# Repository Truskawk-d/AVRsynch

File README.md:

Gra: Sekwencja Przyciskiem

Gra logiczna pozwalająca użytkownikowi na odtworzenie zaprogramowanej sekwencji przycisków. Jeśli gracz wprowadzi poprawną sekwencję w określonym czasie, gra sygnalizuje sukces. W przypadku błędu lub upływu czasu pojawia się sygnał niepowodzenia.

Funkcjonalności
	•	Tryb gry:
	•	Gracz ma za zadanie odtworzyć wcześniej ustaloną sekwencję przycisków.
	•	Limit czasu na odtworzenie całej sekwencji wynosi 10 sekund.
	•	Sukces sygnalizowany jest zapaleniem diody LED Sukces.
	•	Niepowodzenie sygnalizowane jest zapaleniem diody LED Fail.
	•	Tryb konfiguracji sekwencji:
	•	Użytkownik może ustawić własną sekwencję przycisków (4 kroki) za pomocą przycisku konfiguracji.
	•	Nowa sekwencja jest zapamiętywana do następnej konfiguracji.

Wymagania sprzętowe
	•	Mikrokontroler (np. Arduino lub zgodny z AVR)
	•	Przyciski podłączone do portów PD0–PD5
	•	Dwie diody LED (sukces i niepowodzenie) podłączone do PB1 i PB2

Sposób działania
	1.	Start gry:
	•	Naciśnij przycisk start (PD0), aby rozpocząć grę.
	•	Odtwórz zaprogramowaną sekwencję przycisków w odpowiedniej kolejności.
	•	Na poprawną sekwencję masz 10 sekund.
	2.	Konfiguracja sekwencji:
	•	Naciśnij przycisk konfiguracji (PD5), aby przejść do trybu ustawień.
	•	Ustaw nową sekwencję wciskając kolejno cztery przyciski (PD1–PD4).
	•	Po zakończeniu konfiguracji dioda LED Sukces miga dwukrotnie.

Ustawienia
	•	Domyślna sekwencja:
	•	PD1 → PD2 → PD3 → PD4
	•	Czas na wykonanie sekwencji: 10 sekund

Instalacja
	1.	Skopiuj kod do środowiska Arduino IDE lub innego kompatybilnego środowiska.
	2.	Podłącz mikrokontroler według opisanych w kodzie połączeń.
	3.	Wgraj kod na mikrokontroler.

Schemat podłączenia
	•	Przyciski:
	•	PD0: Start gry
	•	PD1–PD4: Kolejne kroki sekwencji
	•	PD5: Tryb konfiguracji
	•	Diody LED:
	•	PB1: Sukces
	•	PB2: Niepowodzenie

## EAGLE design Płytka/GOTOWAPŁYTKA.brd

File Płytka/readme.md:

# Opis płytki PCB

Płytka zaprojektowana do gry z sekwencją przycisków wykorzystuje mikrokontroler AVR (np. ATmega8) i zestaw elementów wspomagających. Oto szczegóły konstrukcji:

## 1. Mikrokontroler
- Centralnym elementem płytki jest mikrokontroler (ATmega8 lub kompatybilny) umieszczony w podstawce DIP28.
- Mikrokontroler jest podłączony do:
  - **Pinów wejściowych**: przyciski podłączone do portu **PD**.
  - **Pinów wyjściowych**: diody LED podłączone do portu **PB**.
  - Kwarcu oscylacyjnego i kondensatorów do generowania zegara.

## 2. Zasilanie
- Płytka jest zasilana poprzez stabilizator napięcia 7805, który zapewnia stabilne 5V dla mikrokontrolera i reszty układu.
- Elementy w układzie zasilania:
  - Kondensatory filtrujące (elektrolityczne i ceramiczne).
  - Diody prostownicze zabezpieczające przed odwrotną polaryzacją.
  - Dławik, który dodatkowo wygładza napięcie zasilania.

## 3. Przyciski
- Na płytce znajduje się 6 przycisków:
  - Jeden do rozpoczęcia gry (PD0).
  - Cztery do odtwarzania sekwencji (PD1–PD4).
  - Jeden do konfiguracji sekwencji (PD5).
- Przyciski są podłączone do portu D mikrokontrolera, a ich stany są odczytywane w kodzie.

## 4. Diody LED
- Na płytce znajdują się dwie diody LED:
  - **LED Sukces**: Podłączona do PB1. Sygnalizuje poprawne odtworzenie sekwencji.
  - **LED Fail**: Podłączona do PB2. Sygnalizuje błędne odtworzenie sekwencji lub upływ czasu.
- Każda dioda ma rezystor ograniczający prąd.

## 5. Oscylator kwarcowy
- Mikrokontroler korzysta z zewnętrznego oscylatora kwarcowego (16 MHz) oraz dwóch kondensatorów ceramicznych (22 pF) do stabilizacji sygnału zegarowego.

## 6. Złącza
- Płytka zawiera następujące złącza:
  - Złącze ISP (In-System Programming) do programowania mikrokontrolera.
  - Złącza zasilania (VCC i GND) dla stabilizatora.
  - Złącza pinów mikrokontrolera wyprowadzone na zewnątrz w celach testowych lub dalszej rozbudowy.

## 7. Elementy zabezpieczające
- Diody i kondensatory filtrujące w układzie zasilania zapewniają ochronę przed zakłóceniami i odwrotnym podłączeniem zasilania.

## 8. Rozmieszczenie na PCB
- Wszystkie elementy zostały rozmieszczone kompaktowo, z minimalizacją długości ścieżek krytycznych (np. dla zasilania).
- Mikrokontroler znajduje się w centralnej części płytki, otoczony przez złącza ISP i elementy wspomagające.
- Przyciski i diody LED są umieszczone w logicznych sekcjach dla łatwego dostępu.

## 9. Sposób montażu
- Wszystkie elementy zostały zaprojektowane jako przewlekane (THT), co ułatwia lutowanie.
- Płytka zawiera opisy elementów (silkscreen), co znacznie ułatwia montaż i identyfikację komponentów.

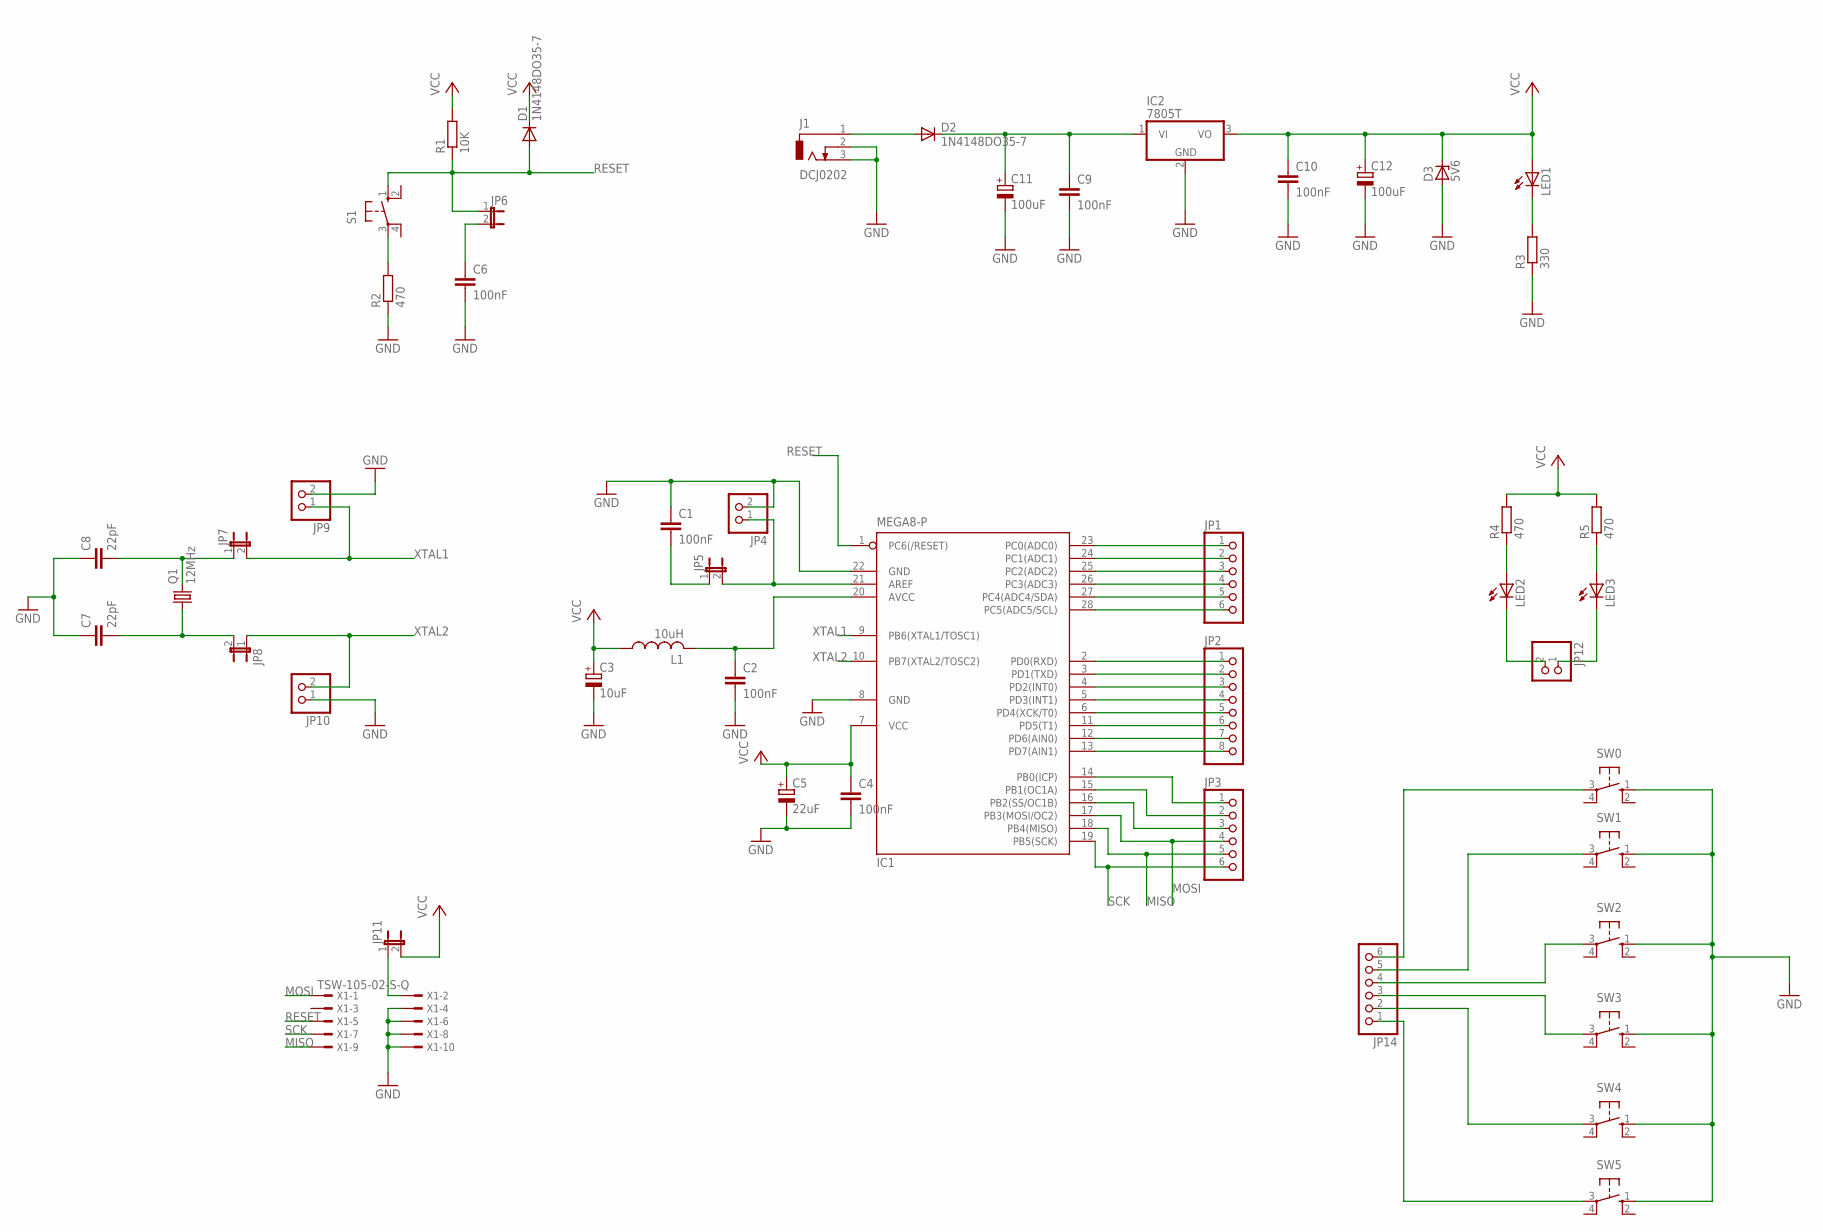
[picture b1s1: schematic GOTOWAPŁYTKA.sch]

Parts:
C1, C2, C4, C6, C9, C10: 100nF; C025-025X050
C3: 10uF; B45181B
C5: 22uF; B45181B
C7, C8: 22pF; C025-025X050
C11, C12: 100uF; B45181B
D1, D2: 1N4148DO35-7; DO35-7
D3: 5V6; C1702-15
IC1: MEGA8-P; DIL28-3
IC2: 7805T; TO220H
J1: DCJ0202
JP1, JP3, JP14: PINHD-1X6; 1X06
JP2: PINHD-1X8; 1X08
JP4, JP9, JP10, JP12: PINHD-1X2; 1X02
JP5, JP6, JP7, JP8, JP11: JP1E; JP1
L1: 10uH; 0204/7
LED1, LED2, LED3: LED5MM
Q1: 12MHz; HC49U-V
R1: 10K; 0204/7
R2, R4, R5: 470; 0204/7
R3: 330; 0204/7
S1: 10-XX; B3F-10XX
SW0, SW1, SW2, SW3, SW4, SW5: 10-XX; B3F-10XX
X1: TSW-105-02-S-Q

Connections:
GND: C1.1, C2.2, C3.-, C4.2, C5.-, C6.2, C7.1, C8.1, C9.2, C10.2, C11.-, C12.-, D3.A, IC1.8 (GND), IC1.22 (GND), IC2.2 (GND), J1.2, J1.3, JP4.2, JP9.2, JP10.1, R2.1, R3.1, SW0.1 (S), SW1.1 (S), SW2.1 (S), SW3.1 (S), SW4.1 (S), SW5.1 (S), X1.4, X1.6, X1.8, X1.10
MISO: IC1.18 (PB4(MISO)), JP3.5, X1.9
MOSI: IC1.17 (PB3(MOSI/OC2)), JP3.4, X1.1
unnamed: C2.1, IC1.20 (AVCC), L1.2
unnamed: C8.2, JP7.1, Q1.2
unnamed: C7.2, JP8.2, Q1.1
unnamed: JP11.1, X1.2
unnamed: IC1.21 (AREF), JP4.1, JP5.2
unnamed: C1.2, JP5.1
unnamed: LED1.K (C), R3.2
unnamed: D2.A, J1.1
unnamed: IC1.23 (PC0(ADC0)), JP1.1
unnamed: IC1.24 (PC1(ADC1)), JP1.2
unnamed: IC1.25 (PC2(ADC2)), JP1.3
unnamed: IC1.26 (PC3(ADC3)), JP1.4
unnamed: IC1.27 (PC4(ADC4/SDA)), JP1.5
unnamed: IC1.28 (PC5(ADC5/SCL)), JP1.6
unnamed: IC1.2 (PD0(RXD)), JP2.1
unnamed: IC1.3 (PD1(TXD)), JP2.2
unnamed: IC1.4 (PD2(INT0)), JP2.3
unnamed: IC1.5 (PD3(INT1)), JP2.4
unnamed: IC1.6 (PD4(XCK/T0)), JP2.5
unnamed: IC1.11 (PD5(T1)), JP2.6
unnamed: IC1.12 (PD6(AIN0)), JP2.7
unnamed: IC1.13 (PD7(AIN1)), JP2.8
unnamed: IC1.14 (PB0(ICP)), JP3.1
unnamed: IC1.15 (PB1(OC1A)), JP3.2
unnamed: IC1.16 (PB2(SS/OC1B)), JP3.3
unnamed: C9.1, C11.+, D2.C, IC2.1 (VI)
unnamed: JP12.1, LED3.K (C)
unnamed: LED3.A, R5.1
unnamed: R2.2, S1.3
unnamed: C6.1, JP6.2
unnamed: JP12.2, LED2.K (C)
unnamed: LED2.A, R4.1
unnamed: JP14.5, SW1.3
unnamed: JP14.4, SW2.3
unnamed: JP14.3, SW3.3
unnamed: JP14.2, SW4.3
unnamed: JP14.6, SW0.3
unnamed: JP14.1, SW5.3
RESET: D1.A, IC1.1 (PC6(/RESET)), JP6.1, R1.1, S1.1 (S), X1.5
SCK: IC1.19 (PB5(SCK)), JP3.6, X1.7
VCC: C3.+, C4.1, C5.+, C10.1, C12.+, D1.C, D3.C, IC1.7 (VCC), IC2.3 (VO), JP11.2, L1.1, LED1.A, R1.2, R4.2, R5.2
XTAL1: IC1.9 (PB6(XTAL1/TOSC1)), JP7.2, JP9.1
XTAL2: IC1.10 (PB7(XTAL2/TOSC2)), JP8.1, JP10.2

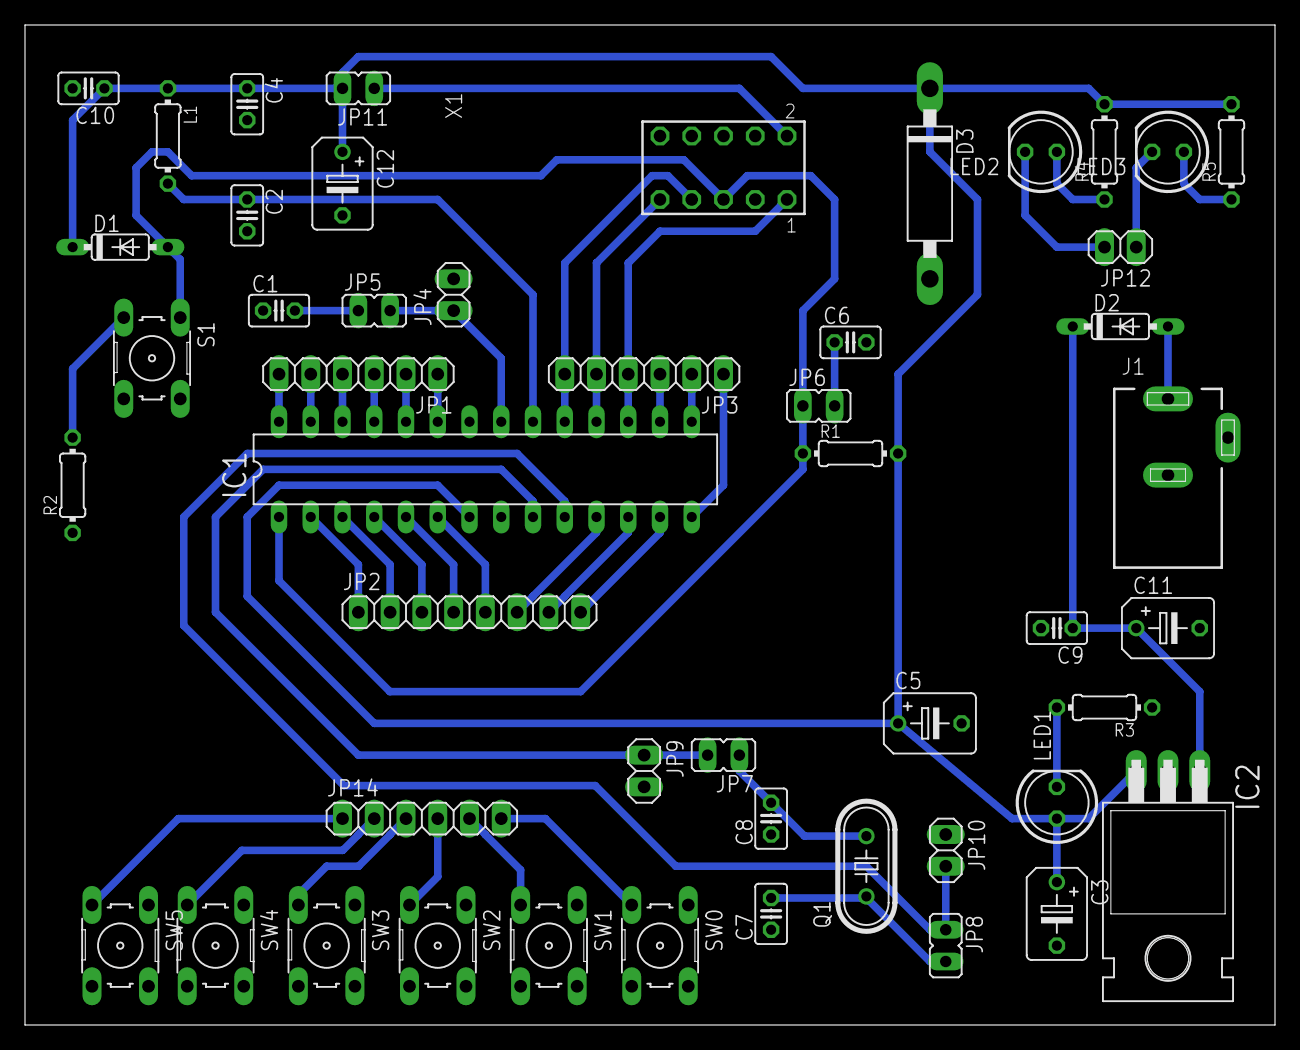
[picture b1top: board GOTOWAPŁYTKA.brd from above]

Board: 2 copper layers, 100.0 x 80.0 mm, 49 parts (0 on the bottom side), 46 nets.

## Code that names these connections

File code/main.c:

// Definicja pinów
const int przyciskStart = PD0; // SW0 - przycisk start
const int przycisk1 = PD1;     // SW1
const int przycisk2 = PD2;     // SW2
const int przycisk3 = PD3;     // SW3
const int przycisk4 = PD4;     // SW4
const int przyciskConfig = PD5; // SW5 - przycisk konfiguracji sekwencji

const int ledSukces = PB1;     // L1 - LED Sukces
const int ledFail = PB2;       // L2 - LED Fail

// Ustawienia sekwencji 
int sekwencja[4] = {przycisk1, przycisk2, przycisk3, przycisk4};
const int dlugoscSekwencji = 4;
const unsigned long czasNaSekwencje = 10000;  // Limit czasu - 10 sekund

void setup() {
  // Ustawienie pinów przycisków z pull-up
  DDRD &= ~((1 << przyciskStart) | (1 << przycisk1) | (1 << przycisk2) | (1 << przycisk3) | (1 << przycisk4) | (1 << przyciskConfig));
  PORTD |= (1 << przyciskStart) | (1 << przycisk1) | (1 << przycisk2) | (1 << przycisk3) | (1 << przycisk4) | (1 << przyciskConfig);

  // Ustawienie pinów LED 
  DDRB |= (1 << ledSukces) | (1 << ledFail);

  // Wyłączenie LED na start
  PORTB &= ~((1 << ledSukces) | (1 << ledFail));
}

void loop() {
  // Sprawdzenie, czy przycisk konfiguracji został wciśnięty
  if (!(PIND & (1 << przyciskConfig))) {
    _delay_ms(200); // Debounce
    
    // Wejście w tryb konfiguracji sekwencji
    konfigurujSekwencje();
  }

  // Sprawdzanie, czy przycisk start został wciśnięty
  if (!(PIND & (1 << przyciskStart))) { // Przycisk start wciśnięty
    _delay_ms(200);  
    unsigned long startCzas = millis();
    int userSequence[dlugoscSekwencji];
    bool sukces = true;

    // Pętla po sekwencji przycisków
    for (int i = 0; i < dlugoscSekwencji; i++) {
      userSequence[i] = -1;
      bool wcisniety = false;

      // Czekanie na wciśnięcie przycisku lub upływ czasu
      while (!wcisniety) {
        // Sprawdzenie, czy minął czas
        if (millis() - startCzas > czasNaSekwencje) {
          sukces = false;
          break;
        }

        // Sprawdzenie, który przycisk został wciśnięty i zapisanie go
        if (!(PIND & (1 << przycisk1))) {
          userSequence[i] = przycisk1;
          wcisniety = true;
          _delay_ms(200);  
        } else if (!(PIND & (1 << przycisk2))) {
          userSequence[i] = przycisk2;
          wcisniety = true;
          _delay_ms(200);  
        } else if (!(PIND & (1 << przycisk3))) {
          userSequence[i] = przycisk3;
          wcisniety = true;
          _delay_ms(200);  
        } else if (!(PIND & (1 << przycisk4))) {
          userSequence[i] = przycisk4;
          wcisniety = true;
          _delay_ms(200);  
        }
      }

      if (!sukces) break;  // Przerwij, jeśli czas minął
    }

    // Porównanie wprowadzonej sekwencji z poprawną sekwencją
    for (int i = 0; i < dlugoscSekwencji; i++) {
      if (userSequence[i] != sekwencja[i]) {
        sukces = false;
        break;
      }
    }

    // Wynik: jeśli sekwencja jest poprawna zapal Sukces, jeśli błędna, zapal Fail
    if (sukces) {
      PORTB |= (1 << ledSukces);  // Zapal LED sukcesu
      _delay_ms(1000);
      PORTB &= ~(1 << ledSukces); // Wyłącz LED sukcesu
    } else {
      PORTB |= (1 << ledFail);  // Zapal LED Fail
      _delay_ms(1000);
      PORTB &= ~(1 << ledFail); // Wyłącz LED Fail
    }
  }
}

void konfigurujSekwencje() {
  // Sygnalizacja wejścia w tryb konfiguracji - mignij LED sukces
  PORTB |= (1 << ledSukces);
  _delay_ms(500);
  PORTB &= ~(1 << ledSukces);
  _delay_ms(500);

  // Oczekiwanie na wprowadzenie nowej sekwencji
  // Użytkownik musi nacisnąć 4 przyciski w żądanej kolejności
  for (int i = 0; i < dlugoscSekwencji; i++) {
    bool wcisniety = false;
    while (!wcisniety) {
      if (!(PIND & (1 << przycisk1))) {
        sekwencja[i] = przycisk1;
        wcisniety = true;
        _delay_ms(200);
      } else if (!(PIND & (1 << przycisk2))) {
        sekwencja[i] = przycisk2;
        wcisniety = true;
        _delay_ms(200);
      } else if (!(PIND & (1 << przycisk3))) {
        sekwencja[i] = przycisk3;
        wcisniety = true;
        _delay_ms(200);
      } else if (!(PIND & (1 << przycisk4))) {
        sekwencja[i] = przycisk4;
        wcisniety = true;
        _delay_ms(200);
      }
    }
  }

  // Potwierdzenie zapisania nowej sekwencji - mignij LED sukces 2 razy
  for (int i = 0; i < 2; i++) {
    PORTB |= (1 << ledSukces);
    _delay_ms(200);
    PORTB &= ~(1 << ledSukces);
    _delay_ms(200);
  }
}
